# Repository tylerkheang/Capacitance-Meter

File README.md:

# Capacitance-Meter
This project is an auto-ranging capacitance meter built with an Arduino UNO and programmed in C++. The device measures capacitance with &lt;1% error by using an NE555 timer for signal generation and a CD4051 analog multiplexer for dynamic range calibration.

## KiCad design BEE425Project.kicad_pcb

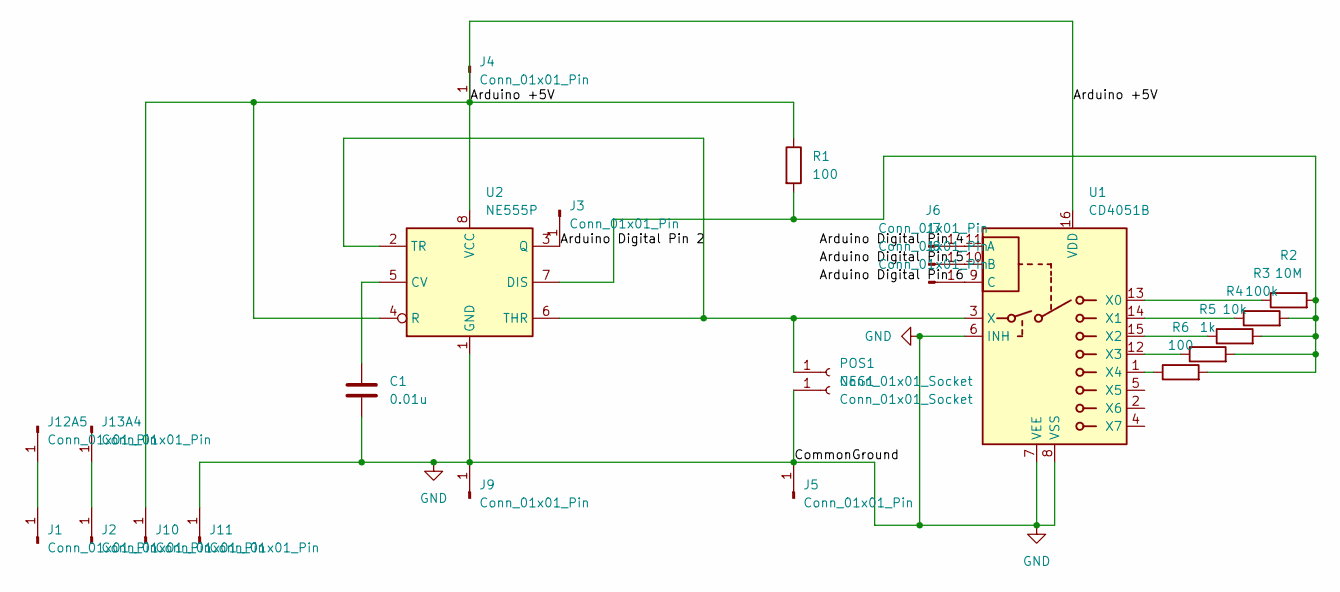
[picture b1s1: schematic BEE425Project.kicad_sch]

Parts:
C1: 0.01u; C_Disc_D3.0mm_W1.6mm_P2.50mm
J1, J2, J3, J4, J5, J6, J7, J8, J9, J10, J11, J12A5, J13A4: Conn_01x01_Pin; PinHeader_1x01_P2.54mm_Vertical
NEG1: Conn_01x01_Socket; PinHeader_1x01_P2.54mm_Vertical
POS1: Conn_01x01_Socket; PinHeader_1x01_P2.54mm_Vertical
R1, R6: 100; R_Axial_DIN0207_L6.3mm_D2.5mm_P10.16mm_Horizontal
R2: 10M; R_Axial_DIN0207_L6.3mm_D2.5mm_P10.16mm_Horizontal
R3: 100k; R_Axial_DIN0207_L6.3mm_D2.5mm_P10.16mm_Horizontal
R4: 10k; R_Axial_DIN0207_L6.3mm_D2.5mm_P10.16mm_Horizontal
R5: 1k; R_Axial_DIN0207_L6.3mm_D2.5mm_P10.16mm_Horizontal
U1: CD4051B; DIP-16_W7.62mm
U2: NE555P; DIP-8_W7.62mm

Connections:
/Arduino +5V: J4.1, J10.1, R1.1, U1.16 (VDD), U2.4 (R), U2.8 (VCC)
/Arduino Digital Pin 2: J3.1, U2.3 (Q)
/Arduino Digital Pin 4: J6.1, U1.11 (A)
/Arduino Digital Pin 5: J7.1, U1.10 (B)
/Arduino Digital Pin 6: J8.1, U1.9 (C)
GND: C1.2, J5.1, J9.1, J11.1, NEG1.1, U1.6 (INH), U1.7 (VEE), U1.8 (VSS), U2.1 (GND)
unnamed: J1.1, J12A5.1
unnamed: J2.1, J13A4.1
unnamed: POS1.1, U1.3 (X), U2.2 (TR), U2.6 (THR)
unnamed: R2.1, U1.13 (X0)
unnamed: R3.1, U1.14 (X1)
unnamed: R4.1, U1.15 (X2)
unnamed: R5.1, U1.12 (X3)
unnamed: R6.1, U1.1 (X4)
unnamed: C1.1, U2.5 (CV)
unnamed: R1.2, R2.2, R3.2, R4.2, R5.2, R6.2, U2.7 (DIS)

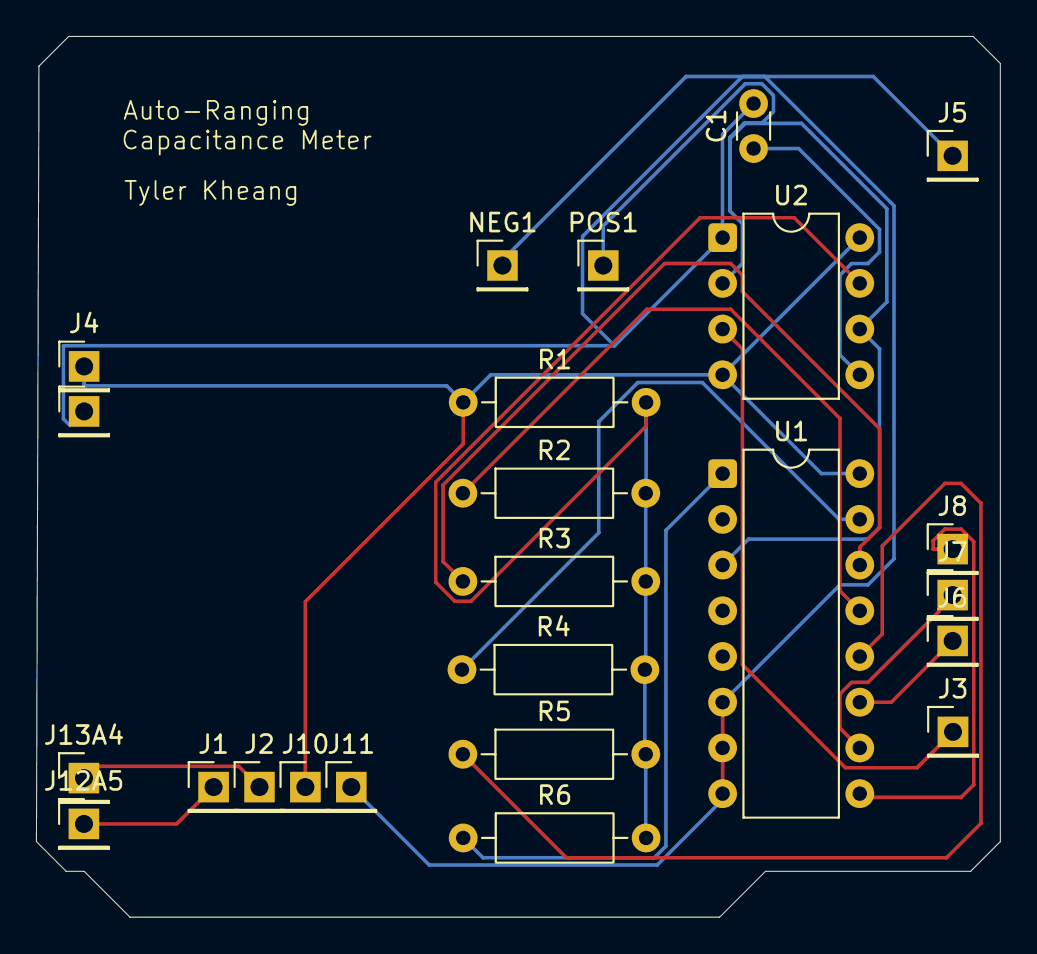
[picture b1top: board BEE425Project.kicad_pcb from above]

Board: 2 copper layers, 53.6 x 48.9 mm, 24 parts (0 on the bottom side), 16 nets.
